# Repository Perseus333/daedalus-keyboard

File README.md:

# Daedalus Keyboard

Daedalus is a compact open-source, split, wireless ergonomic keyboard with trackpad and encoder.

## Daedalus Keyboard

It's a 36 key low-profile, split, wireless, ergonomic keyboard that includes a trackpad and a rotary encoder powered with ZMK on 2 Nice!Nano microcontrollers running on 2 110mAh batteries. It features a key splay inspired from the TOTEM, and a key layout modelled after my hand and inspired by the Corne. It's meant to be portable, silent and unobstrusive thanks to the Ambient Twighlight silent switches and the wireless connectivity.

## Mission

The Daedalus Keyboard has been a hobby project that I worked on during the last year. It has been my first real hardware project that I've done, and I learned a lot throughout the way. Therefore, I aim for this project to be the most open and educational keyboard project possible for everyone.

To that end, here you will find everything needed to get started or to satiate your curiosity: all of the code, the schematics, the CAD files and even my notes during research.

If you're interested in building your own keyboard, then the [report](/docs/report.pdf) might interest you. It is a compreheensive document that describes the whole process of creation of the keyboard step by step, whilst giving some useful tips throughout and some valuable lessons learned at the end.

## Repository Navigation

The repository is split in the following directories:

- **Chassis**: Everything related to the chassis and components that are not hardware - CAD files, drawings and files ready for 3D printing or laser cutting right away
- **Hardware**: Related to the PCB and electronic components - KiCAD schematic and PCB, and even gerber files to submit to a PCB manufacturer
- **Firmware**: The code necessary to run the keyboard - Keybinds, ZMK config, etc.
- **Docs**: The documentation to help you get started building this keyboard or any other - Build log, BOM, research, etc.

## Current development

Currently I'm working on adding to this repository the following, in order:

- Porting the CATIA files into an open source file format
- A contributing/editing guide
- Publishing the Drawings

## Contributing

You're welcome to contribute to this project in any way shape or form that is constructive.

## Licence

This project is licenced differently for each domain, with the intention of promoting open source hardware and software:

- Firmware and code: [GNU Affero General Public License v3 (AGPLv3)](./LICENSE-FIRMWARE)
- Hardware: [CERN Open Hardware License v2 - Strongly Reciprocal](./LICENSE-HARDWARE)
- Documentation and Media: [Creative Commons Attribution-ShareAlike 4.0](https://creativecommons.org/licenses/by-sa/4.0/)

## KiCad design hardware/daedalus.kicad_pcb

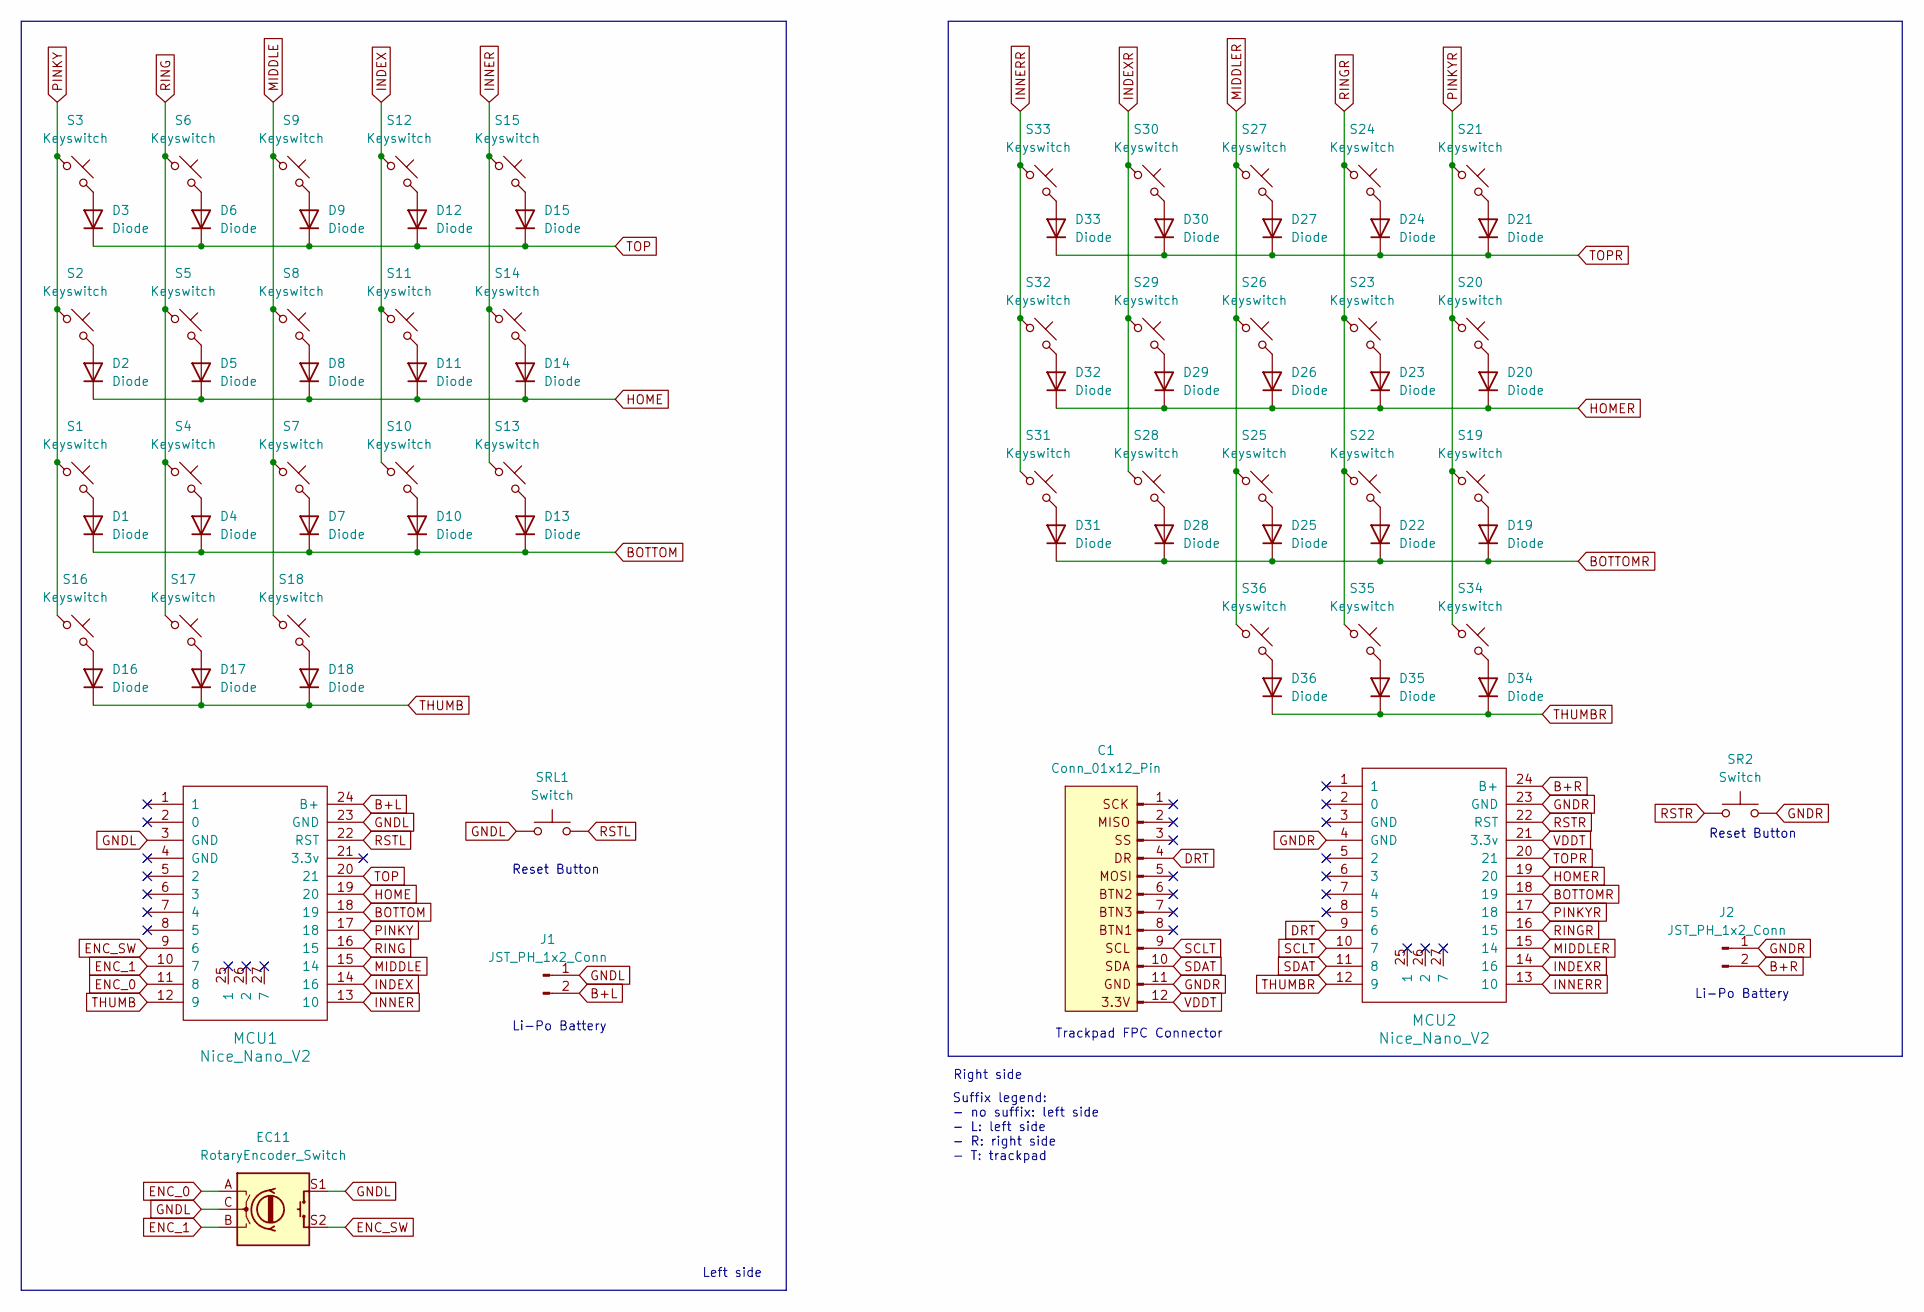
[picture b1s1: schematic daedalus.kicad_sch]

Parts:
C1: Conn_01x12_Pin; Hirose_FH12-12S-0.5SH_1x12-1MP_P0.50mm_Horizontal
D1, D2, D3, D4, D5, D6, D7, D8, D9, D10, D11, D12, D13, D14, D15, D16, D17, D18, D19, D20, D21, D22, D23, D24, D25, D26, D27, D28, D29, D30, D31, D32, D33, D34, D35, D36: Diode; Diode_SOD-123
EC11: RotaryEncoder_Switch; RotaryEncoder_Alps_EC11E-Switch_Vertical_H20mm
J1, J2: JST_PH_1x2_Conn; JST_PH_S2B-PH-SM4-TB_1x02-1MP_P2.00mm_Horizontal
MCU1, MCU2: Nice_Nano_V2
S1, S2, S3, S4, S5, S6, S7, S8, S9, S10, S11, S12, S13, S14, S15, S16, S17, S18, S19, S20, S21, S22, S23, S24, S25, S26, S27, S28, S29, S30, S31, S32, S33, S34, S35, S36: Keyswitch; Choc_V1
SR2: Switch; SW_SPST_CK_KMS2xxG
SRL1: Switch; SW_SPST_CK_KMS2xxG

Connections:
B+L: J1.2, MCU1.24 (B+)
B+R: J2.2, MCU2.24 (B+)
BOTTOM: D1.1 (K), D4.1 (K), D7.1 (K), D10.1 (K), D13.1 (K), MCU1.18 (19)
BOTTOMR: D19.1 (K), D22.1 (K), D25.1 (K), D28.1 (K), D31.1 (K), MCU2.18 (19)
DRT: C1.4, MCU2.9 (6)
ENC_0: EC11.A, MCU1.11 (8)
ENC_1: EC11.B, MCU1.10 (7)
ENC_SW: EC11.S2, MCU1.9 (6)
GNDL: EC11.C, EC11.S1, J1.1, MCU1.3 (GND), MCU1.23 (GND), SRL1.1
GNDR: C1.11, J2.1, MCU2.4 (GND), MCU2.23 (GND), SR2.2
HOME: D2.1 (K), D5.1 (K), D8.1 (K), D11.1 (K), D14.1 (K), MCU1.19 (20)
HOMER: D20.1 (K), D23.1 (K), D26.1 (K), D29.1 (K), D32.1 (K), MCU2.19 (20)
INDEX: MCU1.14 (16), S10.1, S11.1, S12.1
INDEXR: MCU2.14 (16), S28.1, S29.1, S30.1
INNER: MCU1.13 (10), S13.1, S14.1, S15.1
INNERR: MCU2.13 (10), S31.1, S32.1, S33.1
MIDDLE: MCU1.15 (14), S7.1, S8.1, S9.1, S18.1
MIDDLER: MCU2.15 (14), S25.1, S26.1, S27.1, S36.1
unnamed: D1.2 (A), S1.2
unnamed: D2.2 (A), S2.2
unnamed: D3.2 (A), S3.2
unnamed: D4.2 (A), S4.2
unnamed: D5.2 (A), S5.2
unnamed: D6.2 (A), S6.2
unnamed: D7.2 (A), S7.2
unnamed: D8.2 (A), S8.2
unnamed: D9.2 (A), S9.2
unnamed: D10.2 (A), S10.2
unnamed: D11.2 (A), S11.2
unnamed: D12.2 (A), S12.2
unnamed: D13.2 (A), S13.2
unnamed: D14.2 (A), S14.2
unnamed: D15.2 (A), S15.2
unnamed: D16.2 (A), S16.2
unnamed: D17.2 (A), S17.2
unnamed: D18.2 (A), S18.2
unnamed: D19.2 (A), S19.2
unnamed: D20.2 (A), S20.2
unnamed: D21.2 (A), S21.2
unnamed: D22.2 (A), S22.2
unnamed: D23.2 (A), S23.2
unnamed: D24.2 (A), S24.2
unnamed: D25.2 (A), S25.2
unnamed: D26.2 (A), S26.2
unnamed: D27.2 (A), S27.2
unnamed: D28.2 (A), S28.2
unnamed: D29.2 (A), S29.2
unnamed: D30.2 (A), S30.2
unnamed: D31.2 (A), S31.2
unnamed: D32.2 (A), S32.2
unnamed: D33.2 (A), S33.2
unnamed: D34.2 (A), S34.2
unnamed: D35.2 (A), S35.2
unnamed: D36.2 (A), S36.2
PINKY: MCU1.17 (18), S1.1, S2.1, S3.1, S16.1
PINKYR: MCU2.17 (18), S19.1, S20.1, S21.1, S34.1
RING: MCU1.16 (15), S4.1, S5.1, S6.1, S17.1
RINGR: MCU2.16 (15), S22.1, S23.1, S24.1, S35.1
RSTL: MCU1.22 (RST), SRL1.2
RSTR: MCU2.22 (RST), SR2.1
SCLT: C1.9, MCU2.10 (7)
SDAT: C1.10, MCU2.11 (8)
THUMB: D16.1 (K), D17.1 (K), D18.1 (K), MCU1.12 (9)
THUMBR: D34.1 (K), D35.1 (K), D36.1 (K), MCU2.12 (9)
TOP: D3.1 (K), D6.1 (K), D9.1 (K), D12.1 (K), D15.1 (K), MCU1.20 (21)
TOPR: D21.1 (K), D24.1 (K), D27.1 (K), D30.1 (K), D33.1 (K), MCU2.20 (21)
VDDT: C1.12, MCU2.21 (3.3v)

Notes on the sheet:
Right side
Reset Button
Li-Po Battery
Left side
Trackpad FPC Connector
Suffix legend: - no suffix: left side - L: left side - R: right side - T: trackpad

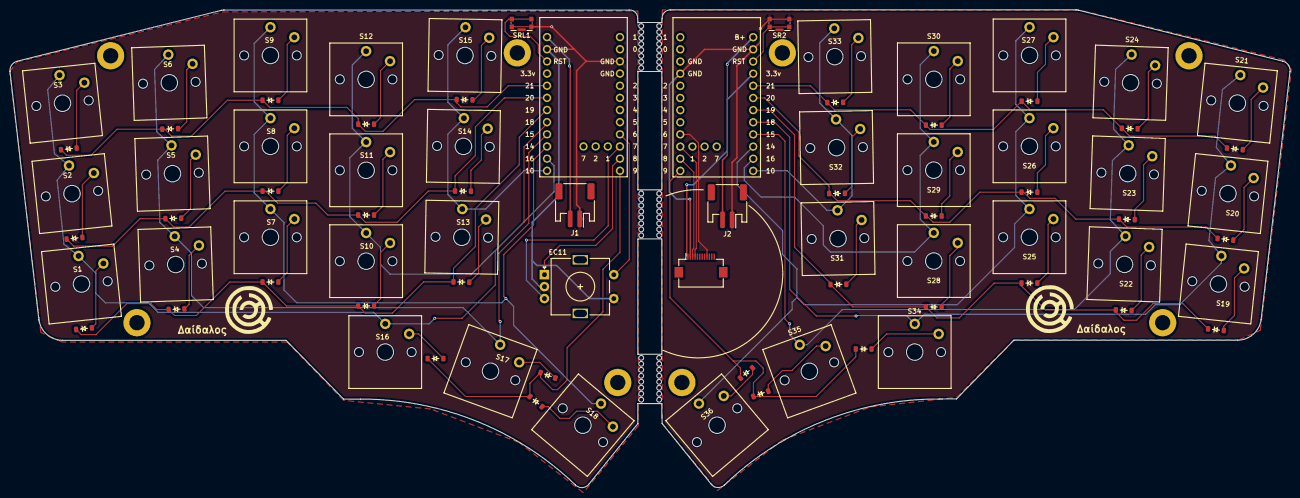
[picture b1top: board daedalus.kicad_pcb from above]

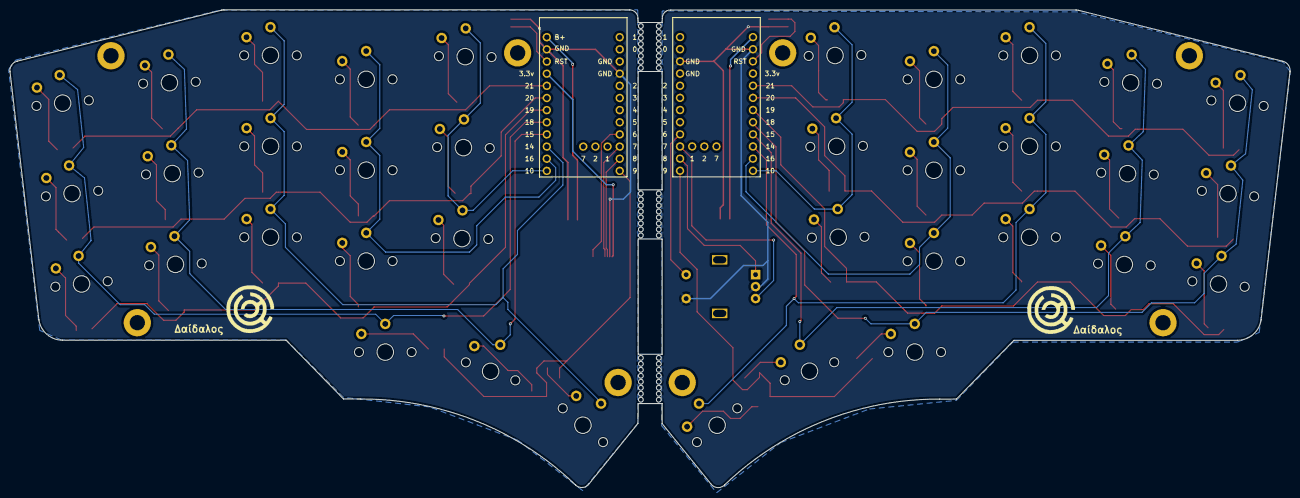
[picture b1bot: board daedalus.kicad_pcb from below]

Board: 2 copper layers, 267.6 x 99.8 mm, 89 parts (2 on the bottom side), 67 nets.

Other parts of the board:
H1, H2, H3, H4, H5, H6, H7, H8: MountingHole_3.2mm_M3_ISO7380_Pad
I: LOGO; daedalus_icon

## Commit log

2025-09-17 feat: initial files
2025-09-17 impr: remove large XCF file
2025-09-17 feat: add joescotto footprints as link
2025-09-18 fix: typo in typst references (thanks to Anton Moisch)
2025-09-18 fix: typo in readme
2025-09-19 feat: add build-guide in PDF
    Compiled with Obsidian
2025-09-19 feat: build guide v1
2025-09-19 impr: simplified footprint paths
2025-09-19 fix: uniform release capitalization
2025-09-19 impr: update firmware submodule
2025-09-19 fix: update readme todo
2025-09-19 fix: minor adjustments to report
